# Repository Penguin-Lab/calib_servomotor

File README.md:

# calib_servomotor
Esse é o calibrador automático de motores servo desenvolvido para agilizar a vida do desenvolvedor de robôs a patas!

## Modo de uso:
Para testar o sistema, o usuário deve:
- Conectar a ESP32 no computador e o motor na PCA9685
- Ligar o sistema com a bateria e pressionar as setas do Game Pad de forma a mexer o eixo do motor e descobrir de forma vaga valores mínimo e máximo de PWM que o motor aceita
- Posicionar de forma vaga o eixo do motor ao centro dessa faixa
- Fixar o motor na estrutura base
- Encaixar o disco no eixo do motor e apeça do ponteiro no disco
- Pressionar o botão quadrado e esperar até que o ponteiro pare na chave fim de curso
- Pressionar o botão círculo e esperar até que o ponteiro pare na chave fim de curso
- Pressionar a cruz para confirmar que o eixo se move para a marcação de centro (0 graus)
- Pressionar o triângulo para escrever no Monitor Serial da IDE do Arduino a faixa de valores para -90 e +90 graus
- Colocar a faixa estimada no arquivo Excel, que retorna a faixa PWM para 0 e 180 graus
- Com o disco posicionado na posição 0 graus, pode-se retirar o motor do sistema e conecta-lo na pata do robô a ser construído

## Aluno participante e desenvolvedor do calibrador automático de servo motor
- Samuel Gurgel Rocha

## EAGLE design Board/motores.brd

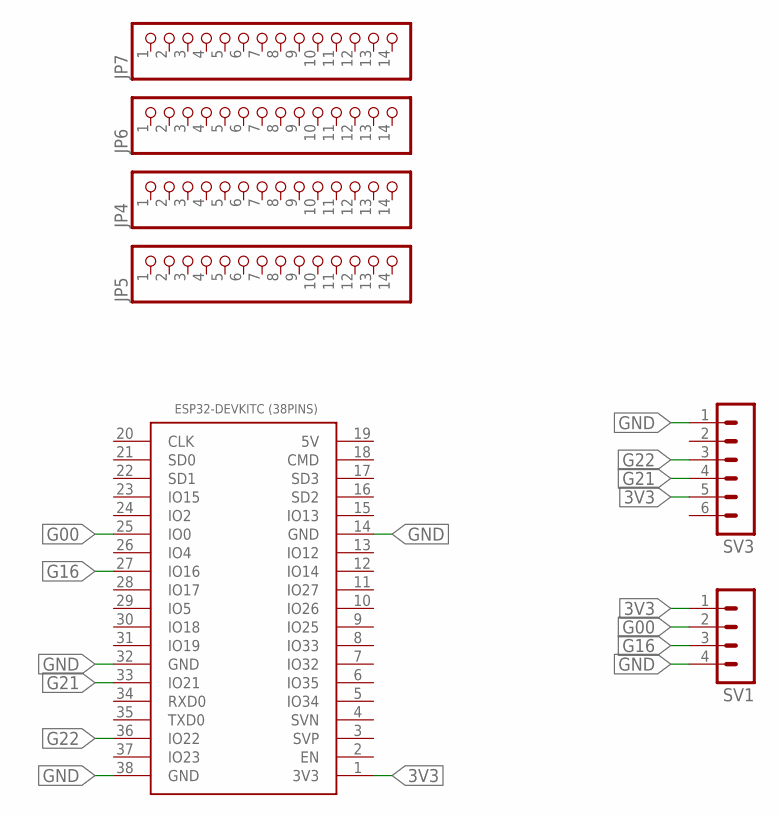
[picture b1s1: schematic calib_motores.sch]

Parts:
ESP32-DEVKITC(38PINS)1: ESP32DEVKITC_38PINS; ESP32-DEVKITC
JP4, JP5, JP6, JP7: PINHD-1X14; 1X14
SV1: MA04-1
SV3: MA06-1

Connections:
3V3: ESP32-DEVKITC(38PINS)1.1 (3V3), SV1.1, SV3.5
G00: ESP32-DEVKITC(38PINS)1.25 (IO0), SV1.2
G16: ESP32-DEVKITC(38PINS)1.27 (IO16), SV1.3
G21: ESP32-DEVKITC(38PINS)1.33 (IO21), SV3.4
G22: ESP32-DEVKITC(38PINS)1.36 (IO22), SV3.3
GND: ESP32-DEVKITC(38PINS)1.14 (GND), ESP32-DEVKITC(38PINS)1.32 (GND), ESP32-DEVKITC(38PINS)1.38 (GND), SV1.4, SV3.1

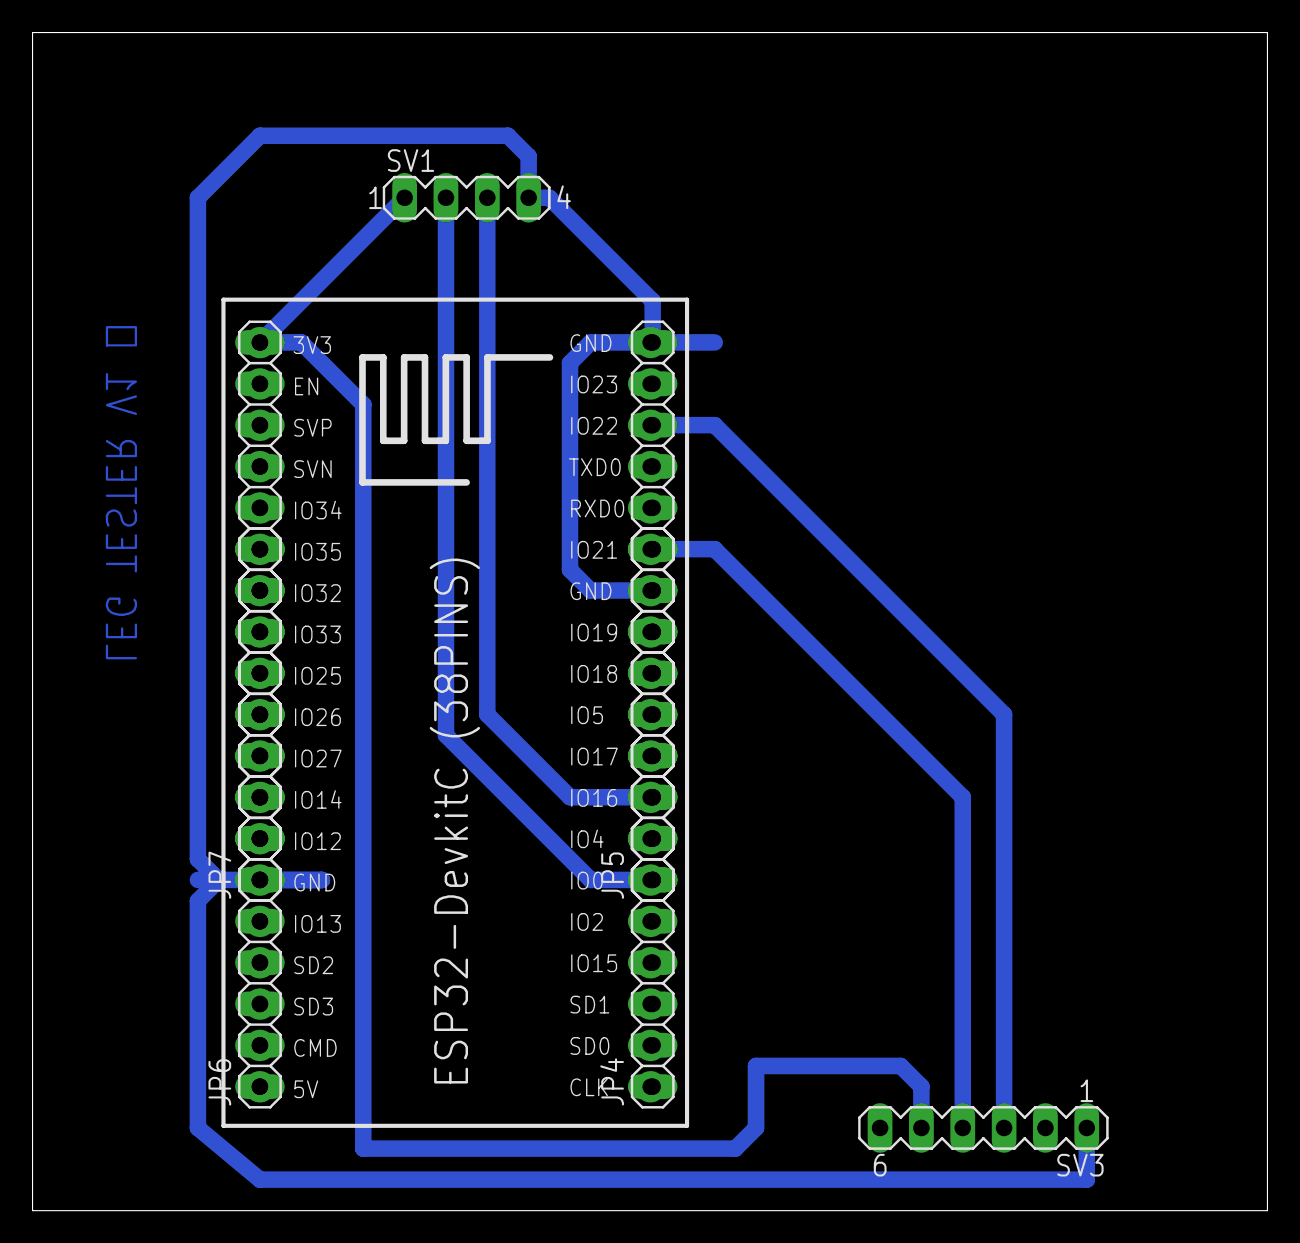
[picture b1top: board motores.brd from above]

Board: 2 copper layers, 75.9 x 72.4 mm, 7 parts (0 on the bottom side), 6 nets.

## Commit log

2025-08-21 Rename CALIB_MOTOR_BASE.SLDPRT to Pecas_3d/CALIB_MOTOR_BASE.SLDPRT
2025-08-21 Rename regradetres.xlsx to Codes/regradetres.xlsx
2025-08-21 Rename calib_motores_3d.ino to Codes/calib_motores_3d.ino
2025-08-21 Rename calib_motores_v1.pdf to Board/calib_motores_v1.pdf
2025-08-21 Rename motores.brd to calib_motores.brd
2025-08-21 Rename motores.sch to calib_motores.sch
